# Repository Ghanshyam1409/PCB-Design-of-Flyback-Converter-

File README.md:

# PCB-Design-of-Closed- Loop-Flyback-Converter-
 PCB Design  of closed loop operation  Flyback Converter 
Flyback converter is DC-DC converter it is isolated converter we use transformer to boost the output voltage as compare to conventional DC-DC converter, Here we design the PCB for closed Loop opreation of Flyback Converter for controlling the output voltage of flyback converter we use type -II Compenstor topology

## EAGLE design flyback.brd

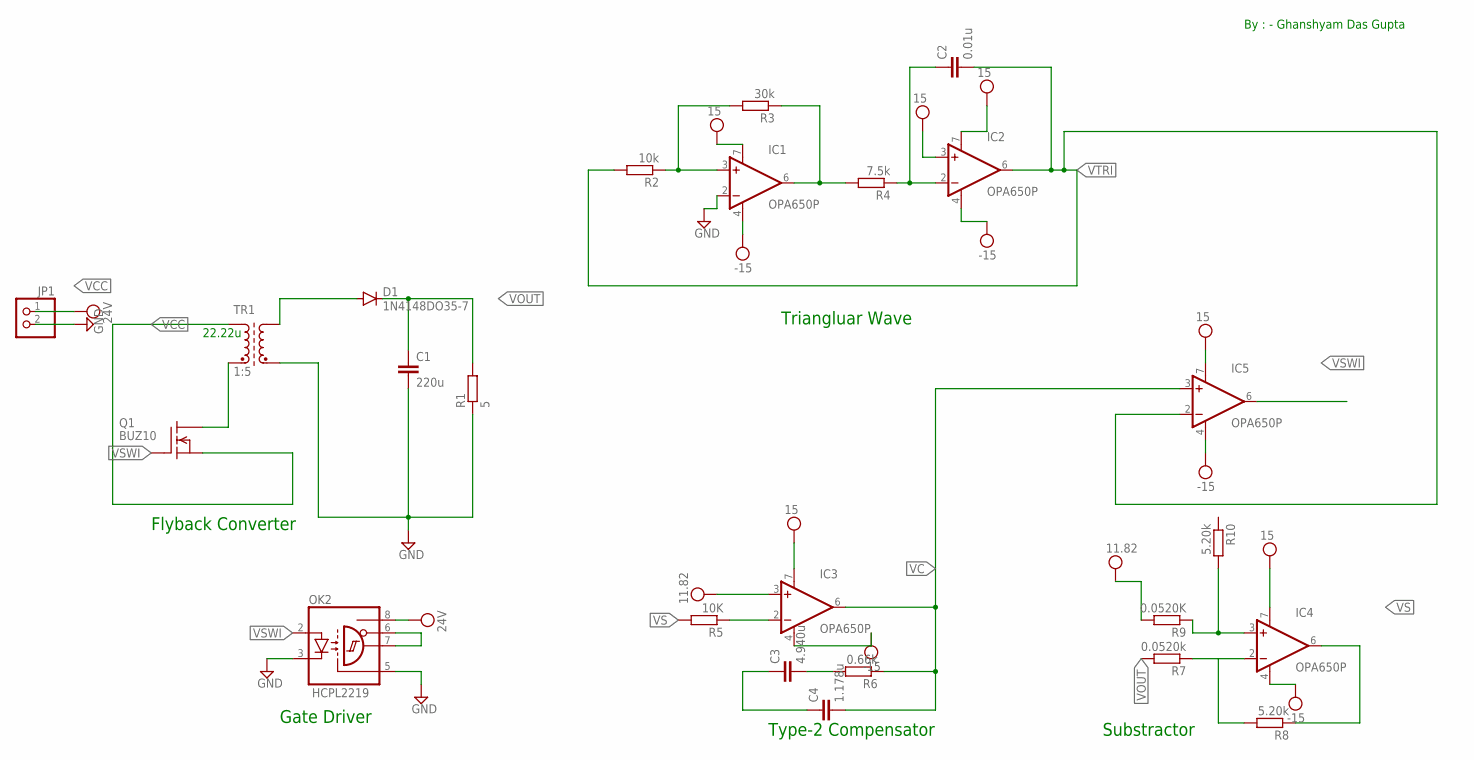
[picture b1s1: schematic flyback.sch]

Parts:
C1: 220u; C050-050X075
C2: 0.01u; C050-050X075
C3: 4.940u; C050-050X075
C4: 1.178u; C050-050X075
D1: 1N4148DO35-7; DO35-7
IC1, IC2, IC3, IC4, IC5: OPA650P; DIL08
JP1: PINHD-1X2; 1X02
OK2: HCPL2219; DIL08
Q1: BUZ10; TO220
R1: 5; 0414/15
R2: 10k; 0414/15
R3: 30k; 0414/15
R4: 7.5k; 0414/15
R5: 10K; 0414/15
R6: 0.66k; 0414/15
R7: 0.0520k; 0414/15
R8, R10: 5.20k; 0414/15
R9: 0.0520K; 0414/15
TR1: 1:5; SM-T4

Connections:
GND: C1.2, IC1.2 (-IN), JP1.2, OK2.3 (C), OK2.5 (GND), R1.1, TR1.4 (E2)
unnamed: Q1.3 (S), TR1.1 (A1)
unnamed: D1.A, TR1.5 (A2)
unnamed: IC1.3 (+IN), R2.1, R3.2
unnamed: OK2.6 (VE), OK2.7 (VO)
unnamed: Q1.2 (D), TR1.2 (E1)
unnamed: IC1.6 (OUT), R3.1, R4.2
unnamed: IC3.2 (-IN), R5.1
unnamed: C3.2, R6.2
unnamed: C2.1, IC2.2 (-IN), R4.1
unnamed: C3.1, C4.1
unnamed: IC4.3 (+IN), R9.1, R10.2
unnamed: IC4.2 (-IN), R7.1, R8.2
VC: C4.2, IC3.6 (OUT), IC5.3 (+IN), R6.1
VCC: IC1.4 (V-), IC1.7 (V+), IC2.3 (+IN), IC2.4 (V-), IC2.7 (V+), IC3.3 (+IN), IC3.4 (V-), IC3.7 (V+), IC4.4 (V-), IC4.7 (V+), IC5.4 (V-), IC5.7 (V+), JP1.1, OK2.8 (VCC), R9.2
VOUT: C1.1, D1.C, R1.2
VS: IC4.6 (OUT), R8.1
VSWI: IC5.6 (OUT)
VTRI: C2.2, IC2.6 (OUT), IC5.2 (-IN), R2.2

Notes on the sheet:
22.22u
By : - Ghanshyam Das Gupta
Flyback Converter
Triangluar Wave
Gate Driver
Type-2 Compensator
Substractor

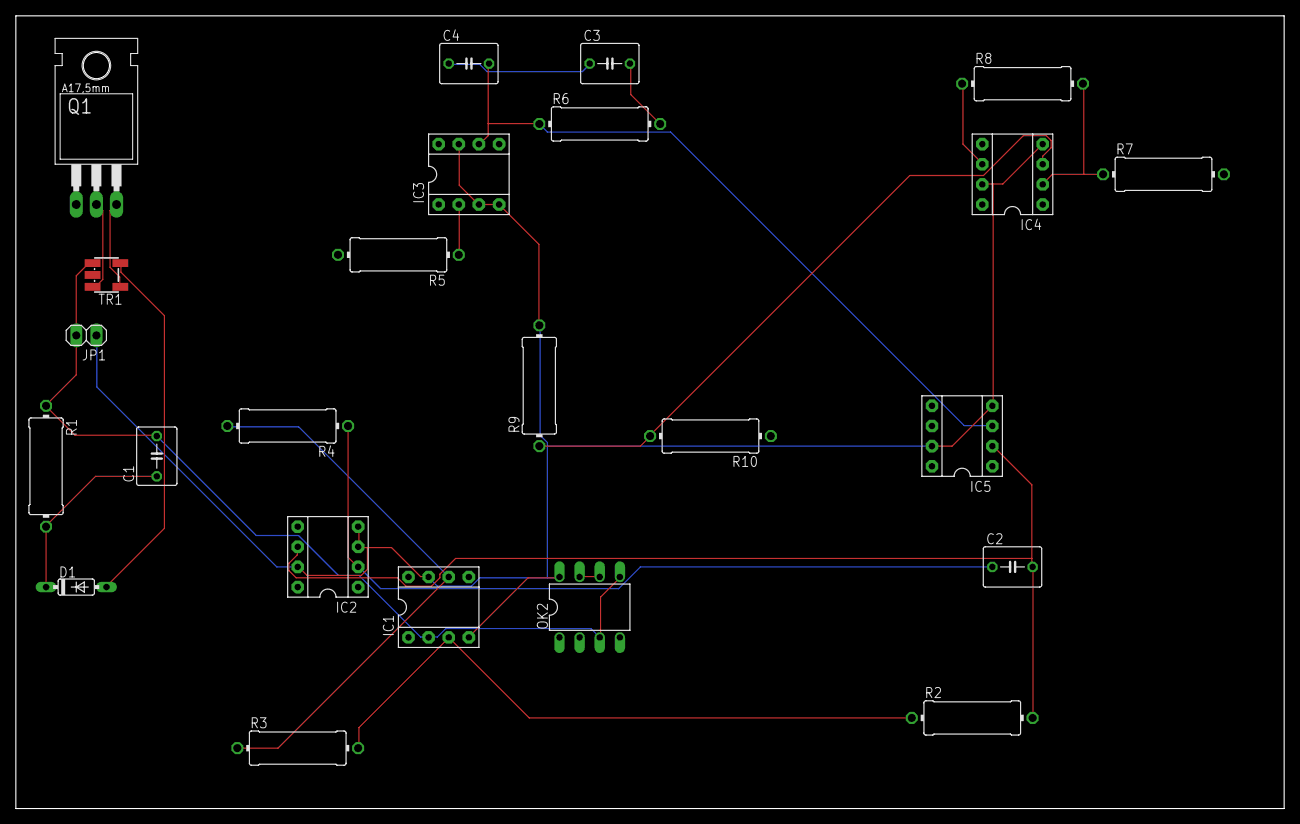
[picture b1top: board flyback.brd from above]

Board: 2 copper layers, 160.0 x 100.0 mm, 24 parts (0 on the bottom side), 18 nets.
